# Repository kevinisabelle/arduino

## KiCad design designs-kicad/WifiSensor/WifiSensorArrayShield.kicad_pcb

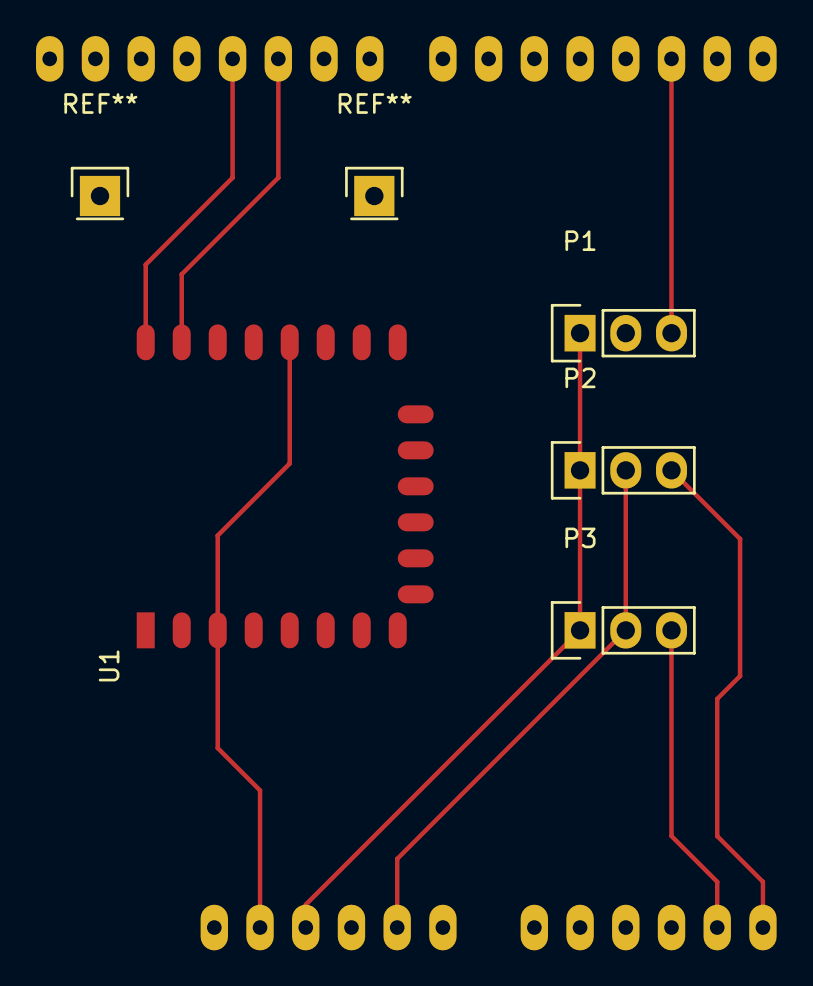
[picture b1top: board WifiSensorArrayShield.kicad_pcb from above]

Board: 2 copper layers, 5 parts (0 on the bottom side), 9 nets.

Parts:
P1: PIR Sensor; Socket_Strip_Straight_1x03
P2: Light Sensor; Socket_Strip_Straight_1x03
P3: Sound Sensor; Socket_Strip_Straight_1x03
U1: ESP-12E
Wifi1: ARDUINO_SHIELD; ARDUINO_SHIELD_2

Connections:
unnamed: P1.1, P2.1, P3.1, Wifi1.5V
unnamed: P1.2, U1.15, U1.16, Wifi1.GND3
unnamed: P1.3, Wifi1.2
unnamed: P2.2, P3.2, Wifi1.GND2
unnamed: P2.3, Wifi1.AD5
unnamed: P3.3, Wifi1.AD4
unnamed: U1.3, U1.8, U1.18, Wifi1.3V3
unnamed: U1.21, Wifi1.10
unnamed: U1.22, Wifi1.11

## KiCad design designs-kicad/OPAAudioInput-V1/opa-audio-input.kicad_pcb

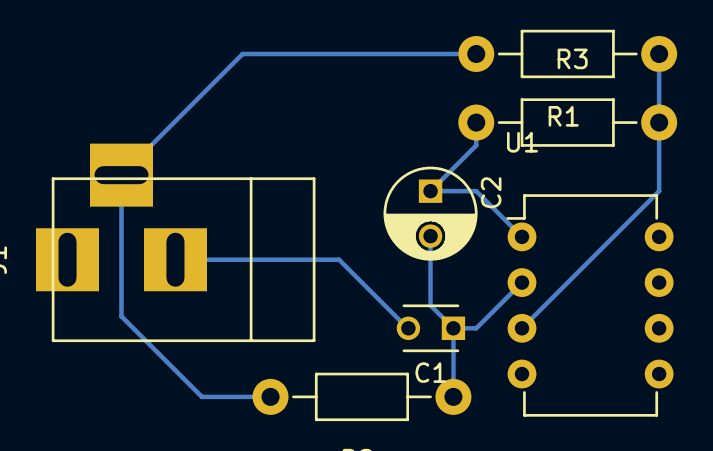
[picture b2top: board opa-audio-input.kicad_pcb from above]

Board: 2 copper layers, 7 parts (0 on the bottom side), 5 nets.

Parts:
C1: 0.1uf; C_Disc_D3_P2.5
C2: 10uf; C_Radial_D5_L11_P2.5
J1: JACK_2P; BARREL_JACK
R1, R2, R3: R; Resistor_Horizontal_RM10mm
U1: TL072; DIP-8_W7.62mm

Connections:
Earth: J1.3, R1.2, R2.2
unnamed: C1.1, C2.2, R2.1, U1.2
unnamed: C1.2, J1.2
unnamed: R1.1, R3.2, U1.3
Output: C2.1, R3.1, U1.1

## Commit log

2015-06-11 no message
2015-07-09 Added multiplexing script
2016-01-25 Update du VU meter pour potentiomettre.
2016-02-10 Pir sensor avec LCD display
2016-02-12 VU meter code.
2016-02-13 SenorPir library
2016-02-15 Multiplex output lib
2016-02-15 Ajout d'une librairie DMX.
2016-02-18 Doorbell fritzing start.
2016-02-28 Ajout de la lib LedControl et project avec jobstick.
2016-02-29 netbeans project for editing.
2016-02-29 Menage et update de PirToCloud.ino
2016-04-11 Neopixels and 433Mhz transeivers.
2016-04-12 Piezo drum module update.
2016-04-13 PiezoDrumModule fritzing diagram
2016-04-20 Arduinoscope basic
2016-04-20 DmxLive with RS485
2016-04-22 PiezoDrum: 2 pots et 2 piezo
2016-05-15 LiquidCrystal I2C et rotary encoder.
2016-05-18 Fritzing vumeter multiplex
2016-05-24 Ki cad start
2016-06-09 Cleanup
2016-06-11 Arduino Wifi sensors shield
2016-08-10 Update MSGEQ7 with LCD I2C screen.
2016-08-11 Adding lights
2017-01-22 MSGEQ7 Board Stereo
2017-02-28 PCB ng smd
2017-03-01 Drum shield first draft.
